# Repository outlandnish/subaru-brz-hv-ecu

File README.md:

# Subaru BRZ HV ECU

> **SAFETY NOTICE:** This system controls high-voltage contactors on a traction battery pack.
> Incorrect firmware can result in arc flash, fire, or electrocution. Do not flash untested builds
> to hardware connected to a live HV pack.

This is the HV ECU for a Subaru BRZ EV conversion. It manages:
- **Battery management** — cell voltage monitoring, balancing, and protection via NXP MC33772 BCC ICs
- **HV contactor control** — precharge, engage, and safe shutdown via DRV8874 H-bridge drivers
- **CAN communication** — IVT-S current/voltage shunt (HV CAN), CHAdeMO EVSE controller (M3 CAN)
- **CANopen** — parameter access and spot-value reporting via libopeninv

## Hardware

See [`hardware/`](hardware/) for schematics and pin maps.

Key specs:
- MCU: STM32F413VH running FreeRTOS
- 16 Taycan modules (8 per BCC chain, two MC33772 chains)
- DRV8874 H-bridge drivers for HV and AC contactors
- IVT-S 1000 A current shunt on HV CAN bus
- CHAdeMO controller (Foccci) on M3 CAN bus

## Getting Started

Clone with submodules:

```bash
git clone --recurse-submodules <repo-url>
# or after a plain clone:
git submodule update --init --recursive
```

## Building and Flashing

This project uses [PlatformIO](https://platformio.org/).

```bash
# Build main firmware
pio run -e hv-ecu

# Flash via ST-Link
pio run -e hv-ecu --target upload

# Serial monitor (115200 baud)
pio device monitor
```

## First-Boot Procedure

1. Flash firmware with ST-Link connected and HV pack **disconnected**.
2. Open a serial monitor at 115200 baud.
3. Type `status` to verify BCC devices are detected and cell voltages are sensible.
4. Type `params` to review default charge parameters before connecting HV.
5. Connect HV pack. Type `hv connect` to initiate precharge sequence.

## Running Tests

Unit tests run on-target via PlatformIO Unity:

```bash
pio test -e bms-test
```

## License

MIT — see [LICENSE](LICENSE).

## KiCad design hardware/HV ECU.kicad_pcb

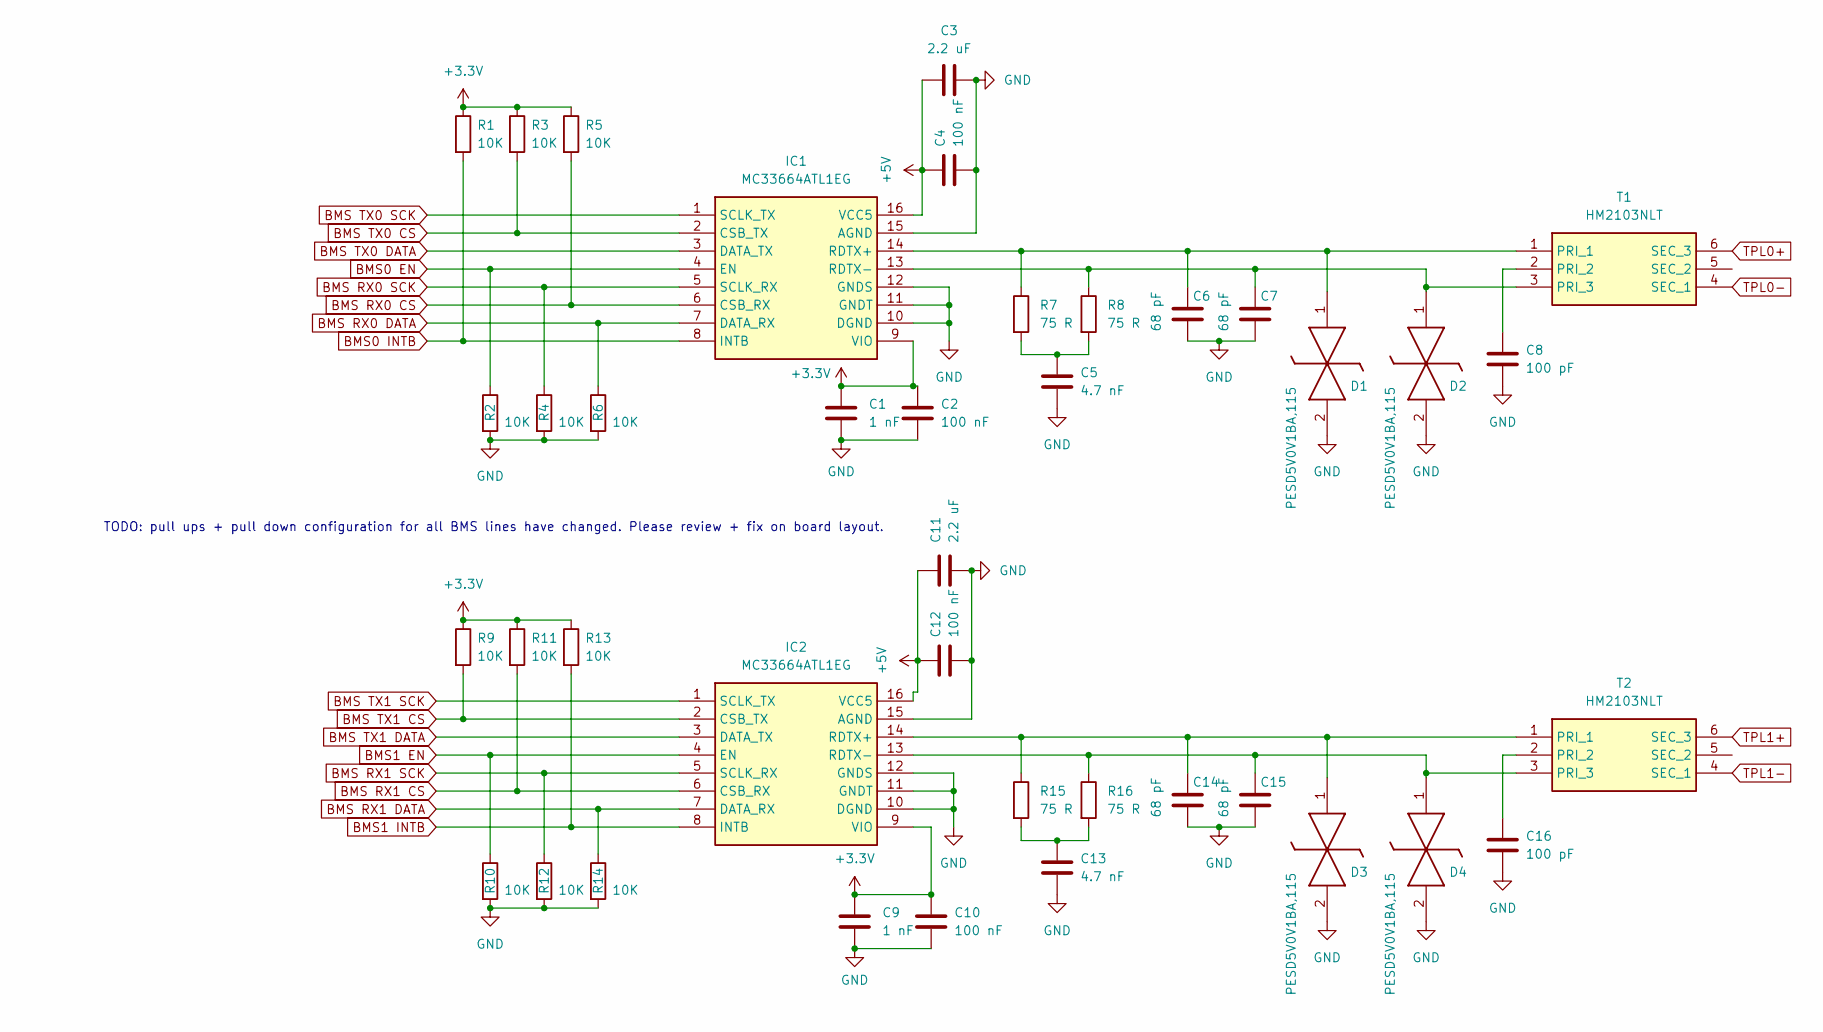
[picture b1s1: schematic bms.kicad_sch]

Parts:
C1, C9: 1 nF; C_0402_1005Metric
C2, C4, C10, C12: 100 nF; C_0402_1005Metric
C3, C11: 2.2 uF; C_0805_2012Metric
C5, C13: 4.7 nF; C_0402_1005Metric
C6, C7, C14, C15: 68 pF; C_0402_1005Metric
C8, C16: 100 pF; C_0402_1005Metric
D1, D2, D3, D4: PESD5V0V1BA,115; SOD2512X110N; Mouser Part Number 771-PESD5V0V1771-BA
IC1, IC2: MC33664ATL1EG; SOIC127P600X175-16N; Mouser Part Number 841-MC33664ATL1EG
R1, R2, R3, R4, R5, R6, R9, R10, R11, R12, R13, R14: 10K; C_0402_1005Metric
R7, R8, R15, R16: 75 R; C_0603_1608Metric
T1, T2: HM2103NLT; SOP254P940X572-6N; Mouser Part Number 673-HM2103NLT

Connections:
+3.3V: C1.1, C2.1, C9.1, C10.1, IC1.9 (VIO), IC2.9 (VIO), R1.1, R3.1, R5.1, R9.1, R11.1, R13.1; also elsewhere on the board
+5V: C3.1, C4.1, C11.1, C12.1, IC1.16 (VCC5), IC2.16 (VCC5); also elsewhere on the board
BMS0 EN: IC1.4 (EN), R2.1
BMS0 INTB: IC1.8 (INTB), R1.2
BMS1 EN: IC2.4 (EN), R10.1
BMS1 INTB: IC2.8 (INTB), R13.2
BMS RX0 CS: IC1.6 (CSB_RX), R5.2
BMS RX0 DATA: IC1.7 (DATA_RX), R6.1
BMS RX0 SCK: IC1.5 (SCLK_RX), R4.1
BMS RX1 CS: IC2.6 (CSB_RX), R11.2
BMS RX1 DATA: IC2.7 (DATA_RX), R14.1
BMS RX1 SCK: IC2.5 (SCLK_RX), R12.1
BMS TX0 CS: IC1.2 (CSB_TX), R3.2
BMS TX0 DATA: IC1.3 (DATA_TX)
BMS TX0 SCK: IC1.1 (SCLK_TX)
BMS TX1 CS: IC2.2 (CSB_TX), R9.2
BMS TX1 DATA: IC2.3 (DATA_TX)
BMS TX1 SCK: IC2.1 (SCLK_TX)
GND: C1.2, C2.2, C3.2, C4.2, C5.2, C6.2, C7.2, C8.2, C9.2, C10.2, C11.2, C12.2, C13.2, C14.2, C15.2, C16.2, D1.2 (K2), D2.2 (K2), D3.2 (K2), D4.2 (K2), IC1.10 (DGND), IC1.11 (GNDT), IC1.12 (GNDS), IC1.15 (AGND), IC2.10 (DGND), IC2.11 (GNDT), IC2.12 (GNDS), IC2.15 (AGND), R2.2, R4.2, R6.2, R10.2, R12.2, R14.2; also elsewhere on the board
unnamed: C5.1, R7.2, R8.2
unnamed: C13.1, R15.2, R16.2
unnamed: C6.1, D1.1 (K1), IC1.14 (RDTX+), R7.1, T1.1 (PRI_1)
unnamed: C7.1, D2.1 (K1), IC1.13 (RDTX-), R8.1, T1.3 (PRI_3)
unnamed: C14.1, D3.1 (K1), IC2.14 (RDTX+), R15.1, T2.1 (PRI_1)
unnamed: C15.1, D4.1 (K1), IC2.13 (RDTX-), R16.1, T2.3 (PRI_3)
unnamed: C8.1, T1.2 (PRI_2)
unnamed: C16.1, T2.2 (PRI_2)
TPL0+: T1.6 (SEC_3); also elsewhere on the board
TPL0-: T1.4 (SEC_1); also elsewhere on the board
TPL1+: T2.6 (SEC_3); also elsewhere on the board
TPL1-: T2.4 (SEC_1); also elsewhere on the board

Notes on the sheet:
TODO: pull ups + pull down configuration for all BMS lines have changed. Please review + fix on board layout.

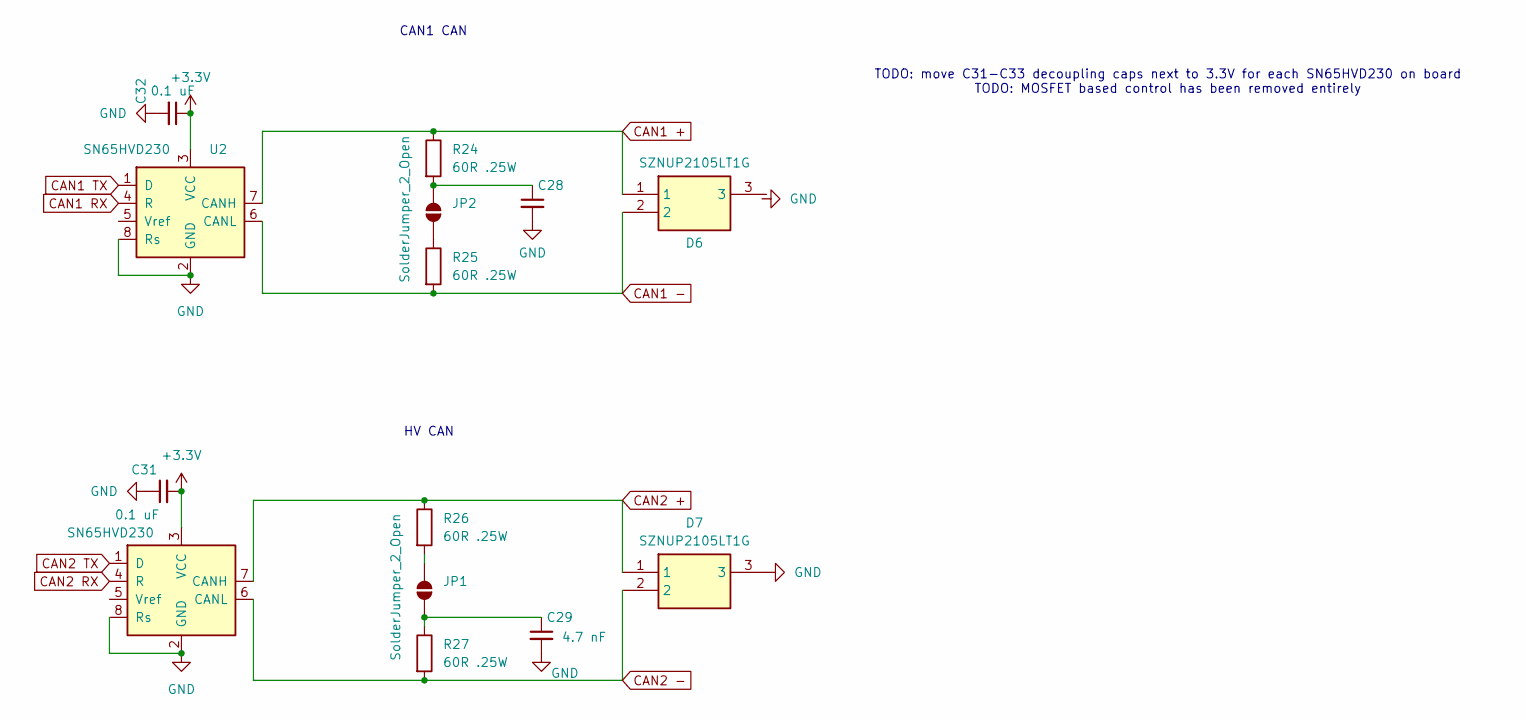
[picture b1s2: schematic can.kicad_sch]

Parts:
C28, C29: 4.7 nF; C_0402_1005Metric
C31, C32: 0.1 uF; C_0402_1005Metric
D6, D7: SZNUP2105LT1G; SOT-23_ONS; Mouser Part Number 863-SZNUP2105LT1G
JP1, JP2: SolderJumper_2_Open; SolderJumper-2_P1.3mm_Open_RoundedPad1.0x1.5mm
R24, R25, R26, R27: 60R .25W; R_0603_1608Metric
U2, U3: SN65HVD230; SOIC-8_3.9x4.9mm_P1.27mm

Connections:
+3.3V: C31.2, C32.1, U2.3 (VCC), U3.3 (VCC); also elsewhere on the board
CAN1 +: D6.1, R24.1, U2.7 (CANH); also elsewhere on the board
CAN1 -: D6.2, R25.2, U2.6 (CANL); also elsewhere on the board
CAN1 RX: U2.4 (R); also elsewhere on the board
CAN1 TX: U2.1 (D); also elsewhere on the board
CAN2 +: D7.1, R26.1, U3.7 (CANH); also elsewhere on the board
CAN2 -: D7.2, R27.2, U3.6 (CANL); also elsewhere on the board
CAN2 RX: U3.4 (R); also elsewhere on the board
CAN2 TX: U3.1 (D); also elsewhere on the board
GND: C28.2, C29.2, C31.1, C32.2, D7.3, U2.2 (GND), U2.8 (Rs), U3.2 (GND), U3.8 (Rs); also elsewhere on the board
unnamed: C29.1, JP1.1 (A), R27.1
unnamed: JP1.2 (B), R26.2
unnamed: JP2.1 (A), R25.1
unnamed: C28.1, JP2.2 (B), R24.2

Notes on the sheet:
CAN1 CAN
HV CAN
TODO: move C31-C33 decoupling caps next to 3.3V for each SN65HVD230 on board TODO: MOSFET based control has been removed entirely

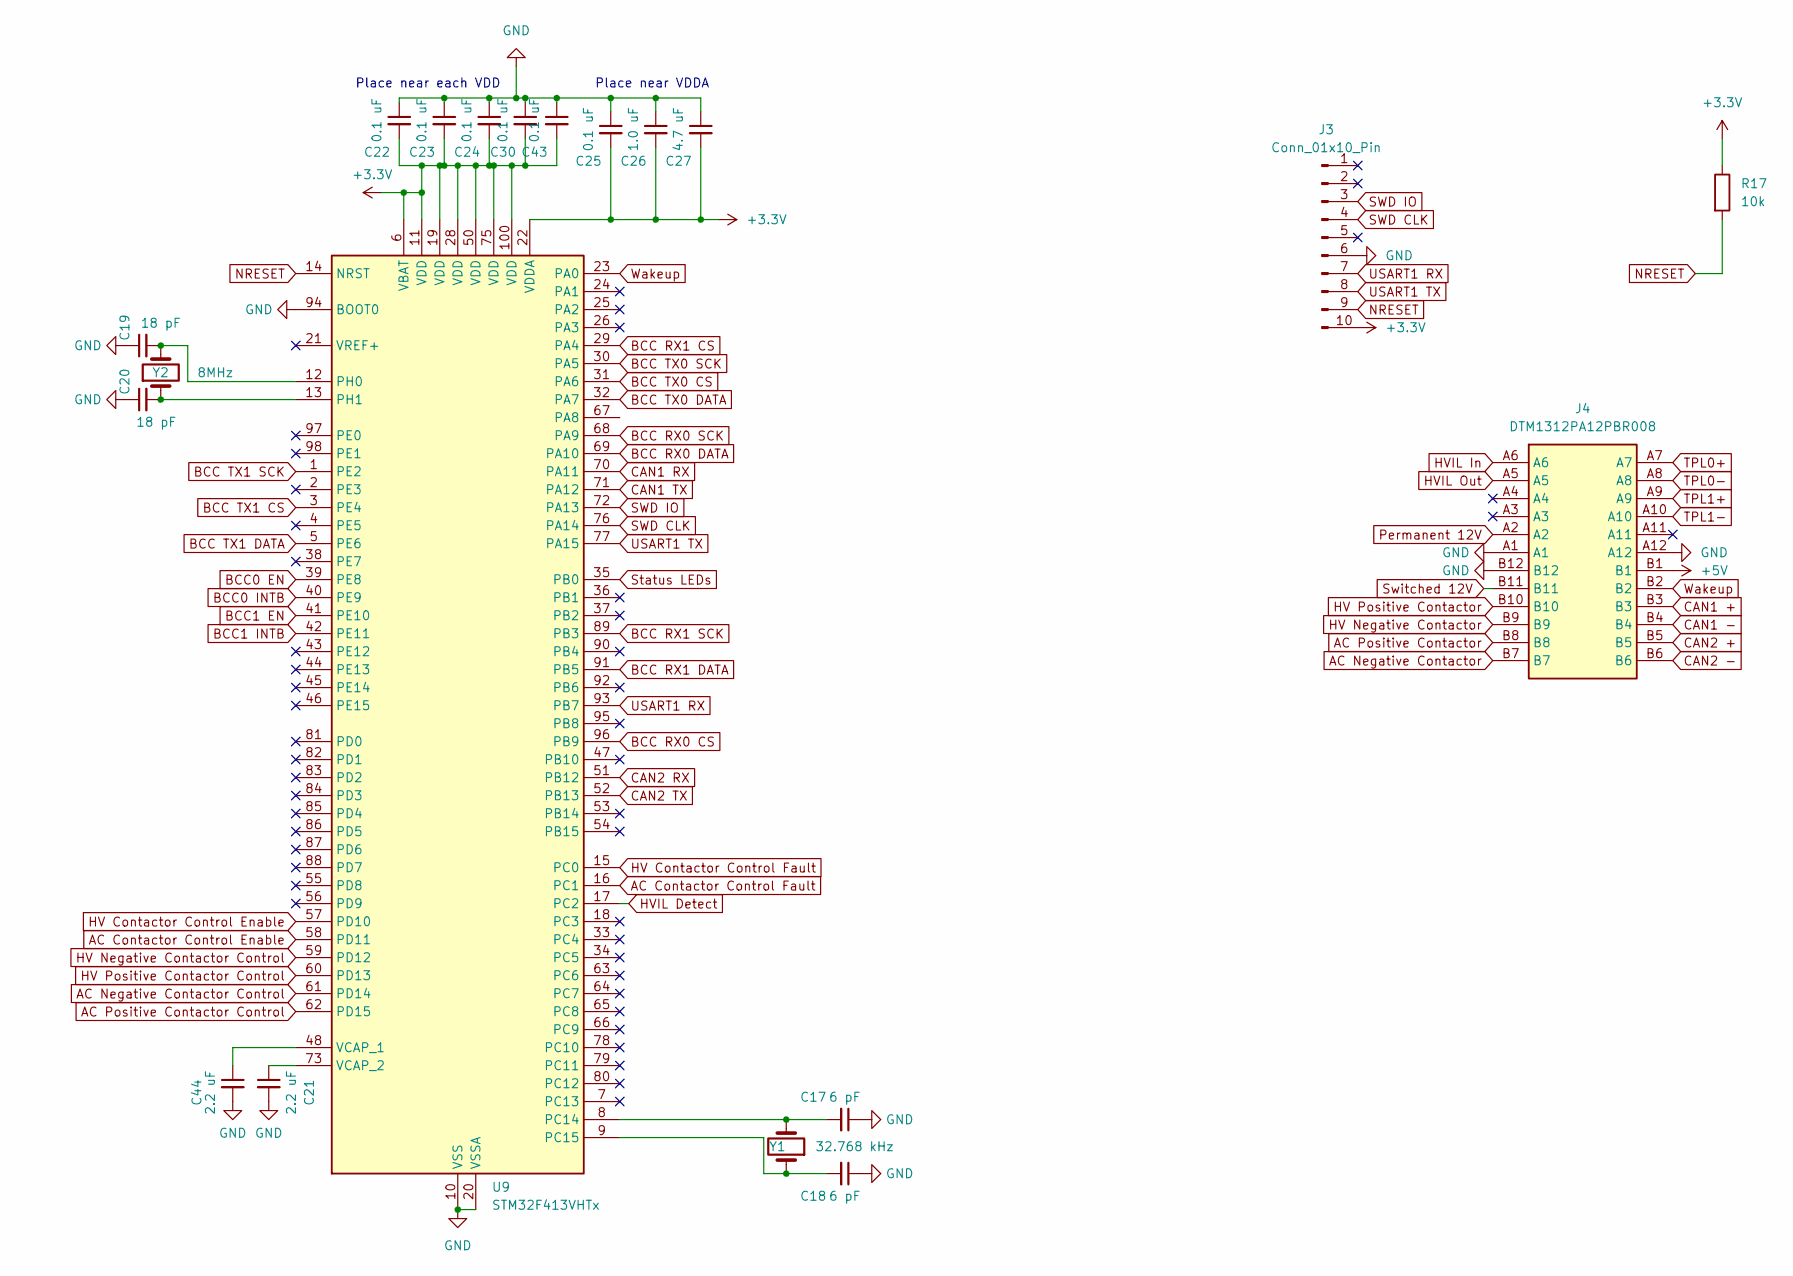
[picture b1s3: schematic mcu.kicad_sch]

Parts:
C17, C18: 6 pF; C_0402_1005Metric
C19, C20: 18 pF; C_0402_1005Metric
C21, C44: 2.2 uF; C_0805_2012Metric
C22, C23, C24, C25, C30, C43: 0.1 uF; C_0402_1005Metric
C26: 1.0 uF; C_0402_1005Metric
C27: 4.7 uF; C_0805_2012Metric
J3: Conn_01x10_Pin; ST-Link MINIV3 BTB
J4: DTM1312PA12PBR008; Mouser Part Number 571-TM1312PA12PBR008
R17: 10k; R_0603_1608Metric
U9: STM32F413VHTx; LQFP-100_14x14mm_P0.5mm
Y1: 32.768 kHz; Crystal_SMD_3215-2Pin_3.2x1.5mm
Y2: 8MHz; Crystal_SMD_HC49-SD

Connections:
+3.3V: C22.2, C23.2, C24.2, C25.2, C26.2, C27.2, C30.2, C43.2, J3.10, R17.1, U9.6 (VBAT), U9.11 (VDD), U9.19 (VDD), U9.22 (VDDA), U9.28 (VDD), U9.50 (VDD), U9.75 (VDD), U9.100 (VDD); also elsewhere on the board
+5V: J4.B1; also elsewhere on the board
AC Contactor Control Enable: U9.58 (PD11); also elsewhere on the board
AC Contactor Control Fault: U9.16 (PC1); also elsewhere on the board
AC Negative Contactor: J4.B7; also elsewhere on the board
AC Negative Contactor Control: U9.61 (PD14); also elsewhere on the board
AC Positive Contactor: J4.B8; also elsewhere on the board
AC Positive Contactor Control: U9.62 (PD15); also elsewhere on the board
BCC0 EN: U9.39 (PE8)
BCC0 INTB: U9.40 (PE9)
BCC1 EN: U9.41 (PE10)
BCC1 INTB: U9.42 (PE11)
BCC RX0 CS: U9.96 (PB9)
BCC RX0 DATA: U9.69 (PA10)
BCC RX0 SCK: U9.68 (PA9)
BCC RX1 CS: U9.29 (PA4)
BCC RX1 DATA: U9.91 (PB5)
BCC RX1 SCK: U9.89 (PB3)
BCC TX0 CS: U9.31 (PA6)
BCC TX0 DATA: U9.32 (PA7)
BCC TX0 SCK: U9.30 (PA5)
BCC TX1 CS: U9.3 (PE4)
BCC TX1 DATA: U9.5 (PE6)
BCC TX1 SCK: U9.1 (PE2)
CAN1 +: J4.B3; also elsewhere on the board
CAN1 -: J4.B4; also elsewhere on the board
CAN1 RX: U9.70 (PA11); also elsewhere on the board
CAN1 TX: U9.71 (PA12); also elsewhere on the board
CAN2 +: J4.B5; also elsewhere on the board
CAN2 -: J4.B6; also elsewhere on the board
CAN2 RX: U9.51 (PB12); also elsewhere on the board
CAN2 TX: U9.52 (PB13); also elsewhere on the board
GND: C17.1, C18.1, C19.1, C20.1, C21.2, C22.1, C23.1, C24.1, C25.1, C26.1, C27.1, C30.1, C43.1, C44.2, J3.6, J4.A1, J4.A12, J4.B12, U9.10 (VSS), U9.20 (VSSA), U9.27 (VSS), U9.49 (VSS), U9.74 (VSS), U9.94 (BOOT0), U9.99 (VSS); also elsewhere on the board
HV Contactor Control Enable: U9.57 (PD10); also elsewhere on the board
HV Contactor Control Fault: U9.15 (PC0); also elsewhere on the board
HV Negative Contactor: J4.B9; also elsewhere on the board
HV Negative Contactor Control: U9.59 (PD12); also elsewhere on the board
HV Positive Contactor: J4.B10; also elsewhere on the board
HV Positive Contactor Control: U9.60 (PD13); also elsewhere on the board
HVIL Detect: U9.17 (PC2); also elsewhere on the board
HVIL In: J4.A6; also elsewhere on the board
NRESET: J3.9, R17.2, U9.14 (NRST)
unnamed: C17.2, U9.8 (PC14), Y1.2
unnamed: C18.2, U9.9 (PC15), Y1.1
unnamed: C19.2, U9.12 (PH0), Y2.2
unnamed: C20.2, U9.13 (PH1), Y2.1
unnamed: C44.1, U9.48 (VCAP_1)
unnamed: C21.1, U9.73 (VCAP_2)
Permanent 12V: J4.A2; also elsewhere on the board
SWD CLK: J3.4, U9.76 (PA14)
SWD IO: J3.3, U9.72 (PA13)
Status LEDs: U9.35 (PB0); also elsewhere on the board
Switched 12V: J4.B11; also elsewhere on the board
TPL0+: J4.A7; also elsewhere on the board
TPL0-: J4.A8; also elsewhere on the board
TPL1+: J4.A9; also elsewhere on the board
TPL1-: J4.A10; also elsewhere on the board
USART1 RX: J3.7, U9.93 (PB7)
USART1 TX: J3.8, U9.77 (PA15)
Wakeup: J4.B2, U9.23 (PA0)

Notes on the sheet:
Place near each VDD
Place near VDDA

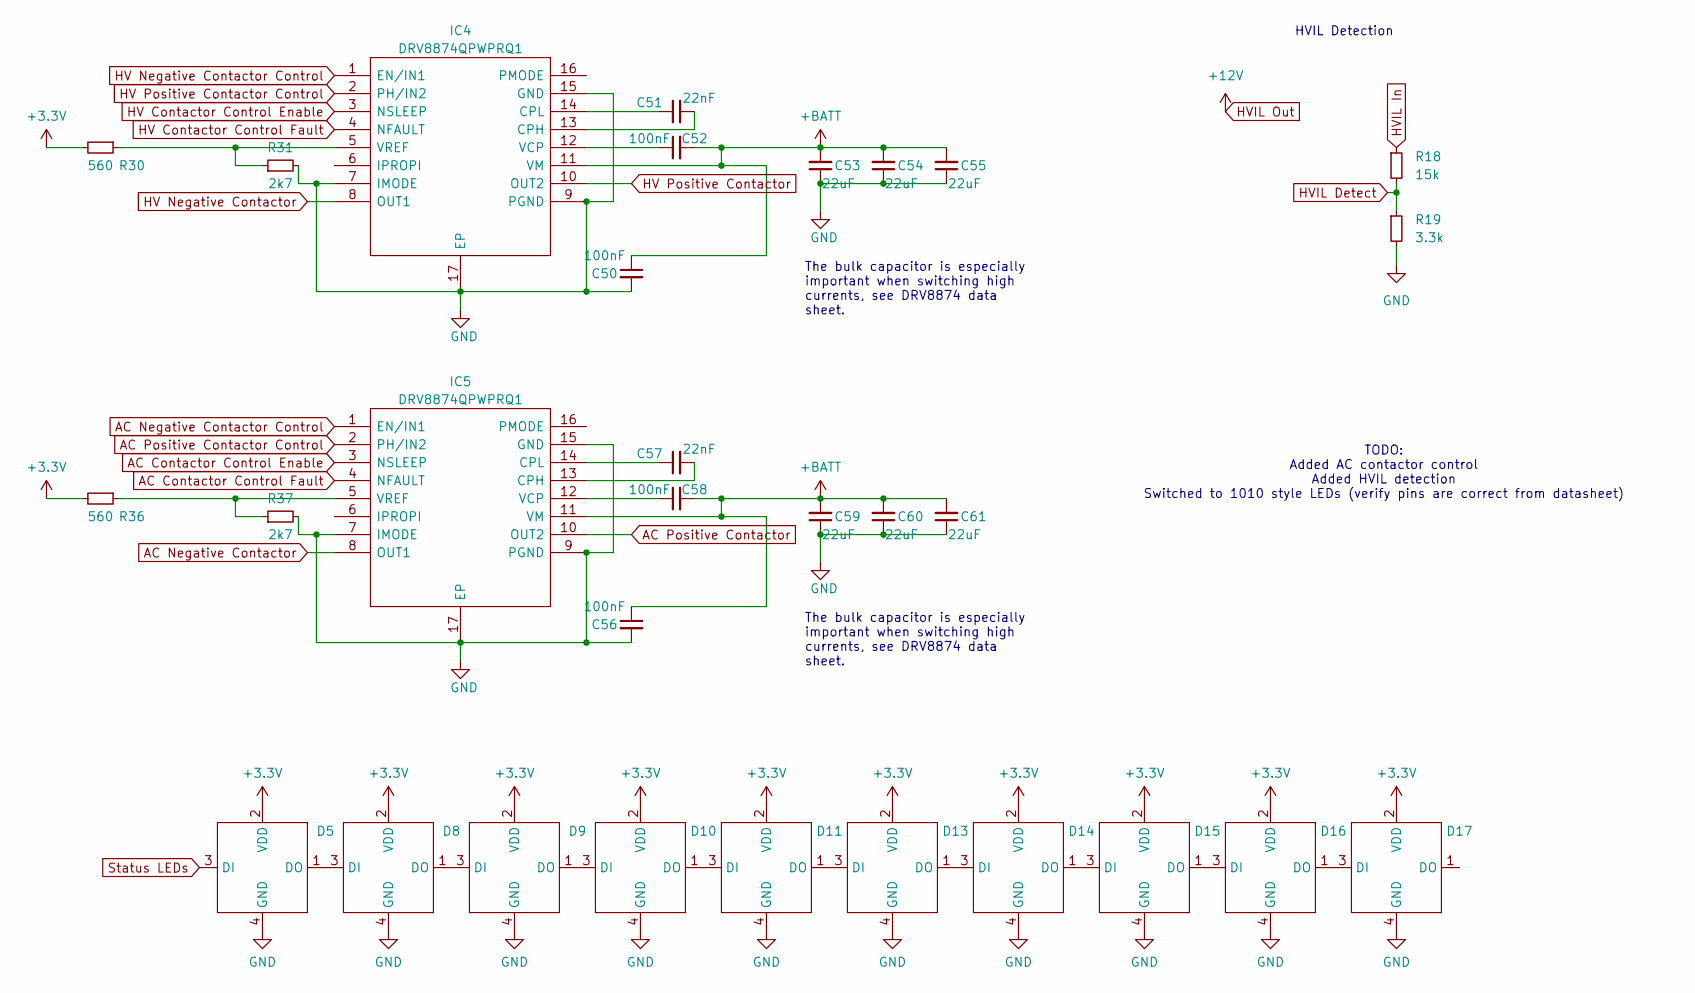
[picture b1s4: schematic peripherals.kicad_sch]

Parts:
C50, C52, C56, C58: 100nF; C_0805_2012Metric_Pad1.18x1.45mm_HandSolder; LCSC C49678
C51, C57: 22nF; C_0805_2012Metric_Pad1.18x1.45mm_HandSolder; LCSC C1729
C53, C54, C55, C59, C60, C61: 22uF; C_1210_3225Metric_Pad1.33x2.70mm_HandSolder; LCSC C12891
D5, D8, D9, D10, D11, D13, D14, D15, D16, D17: XL-1010RGBC-WS2812B
IC4, IC5: DRV8874QPWPRQ1; SOP65P640X120-17N; Mouser Part Number 595-DRV8874QPWPRQ1
R18: 15k; R_0402_1005Metric_Pad0.72x0.64mm_HandSolder
R19: 3.3k; R_0402_1005Metric_Pad0.72x0.64mm_HandSolder
R30, R36: 560; R_0805_2012Metric_Pad1.20x1.40mm_HandSolder; LCSC C28636
R31, R37: 2k7; R_0805_2012Metric_Pad1.20x1.40mm_HandSolder; LCSC C17530

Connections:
+3.3V: D5.2 (VDD), D8.2 (VDD), D9.2 (VDD), D10.2 (VDD), D11.2 (VDD), D13.2 (VDD), D14.2 (VDD), D15.2 (VDD), D16.2 (VDD), D17.2 (VDD), R30.2, R36.2; also elsewhere on the board
+BATT: C50.1, C52.2, C53.2, C54.2, C55.2, C56.1, C58.2, C59.2, C60.2, C61.2, IC4.11 (VM), IC5.11 (VM); also elsewhere on the board
AC Contactor Control Enable: IC5.3 (NSLEEP); also elsewhere on the board
AC Contactor Control Fault: IC5.4 (NFAULT); also elsewhere on the board
AC Negative Contactor: IC5.8 (OUT1); also elsewhere on the board
AC Negative Contactor Control: IC5.1 (EN/IN1); also elsewhere on the board
AC Positive Contactor: IC5.10 (OUT2); also elsewhere on the board
AC Positive Contactor Control: IC5.2 (PH/IN2); also elsewhere on the board
GND: C50.2, C53.1, C54.1, C55.1, C56.2, C59.1, C60.1, C61.1, D5.4 (GND), D8.4 (GND), D9.4 (GND), D10.4 (GND), D11.4 (GND), D13.4 (GND), D14.4 (GND), D15.4 (GND), D16.4 (GND), D17.4 (GND), IC4.7 (IMODE), IC4.9 (PGND), IC4.15 (GND), IC4.17 (EP), IC5.7 (IMODE), IC5.9 (PGND), IC5.15 (GND), IC5.17 (EP), R19.2, R31.2, R37.2; also elsewhere on the board
HV Contactor Control Enable: IC4.3 (NSLEEP); also elsewhere on the board
HV Contactor Control Fault: IC4.4 (NFAULT); also elsewhere on the board
HV Negative Contactor: IC4.8 (OUT1); also elsewhere on the board
HV Negative Contactor Control: IC4.1 (EN/IN1); also elsewhere on the board
HV Positive Contactor: IC4.10 (OUT2); also elsewhere on the board
HV Positive Contactor Control: IC4.2 (PH/IN2); also elsewhere on the board
HVIL Detect: R18.2, R19.1; also elsewhere on the board
HVIL In: R18.1; also elsewhere on the board
unnamed: D5.1 (DO), D8.3 (DI)
unnamed: D8.1 (DO), D9.3 (DI)
unnamed: D9.1 (DO), D10.3 (DI)
unnamed: D10.1 (DO), D11.3 (DI)
unnamed: D11.1 (DO), D13.3 (DI)
unnamed: D13.1 (DO), D14.3 (DI)
unnamed: D14.1 (DO), D15.3 (DI)
unnamed: D15.1 (DO), D16.3 (DI)
unnamed: D16.1 (DO), D17.3 (DI)
unnamed: C51.2, IC4.13 (CPH)
unnamed: C51.1, IC4.14 (CPL)
unnamed: C52.1, IC4.12 (VCP)
unnamed: IC4.5 (VREF), R30.1, R31.1
unnamed: C57.2, IC5.13 (CPH)
unnamed: C57.1, IC5.14 (CPL)
unnamed: C58.1, IC5.12 (VCP)
unnamed: IC5.5 (VREF), R36.1, R37.1
Status LEDs: D5.3 (DI); also elsewhere on the board

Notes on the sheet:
HVIL Detection
The bulk capacitor is especially important when switching high currents, see DRV8874 data sheet.
TODO: Added AC contactor control Added HVIL detection Switched to 1010 style LEDs (verify pins are correct from datasheet)

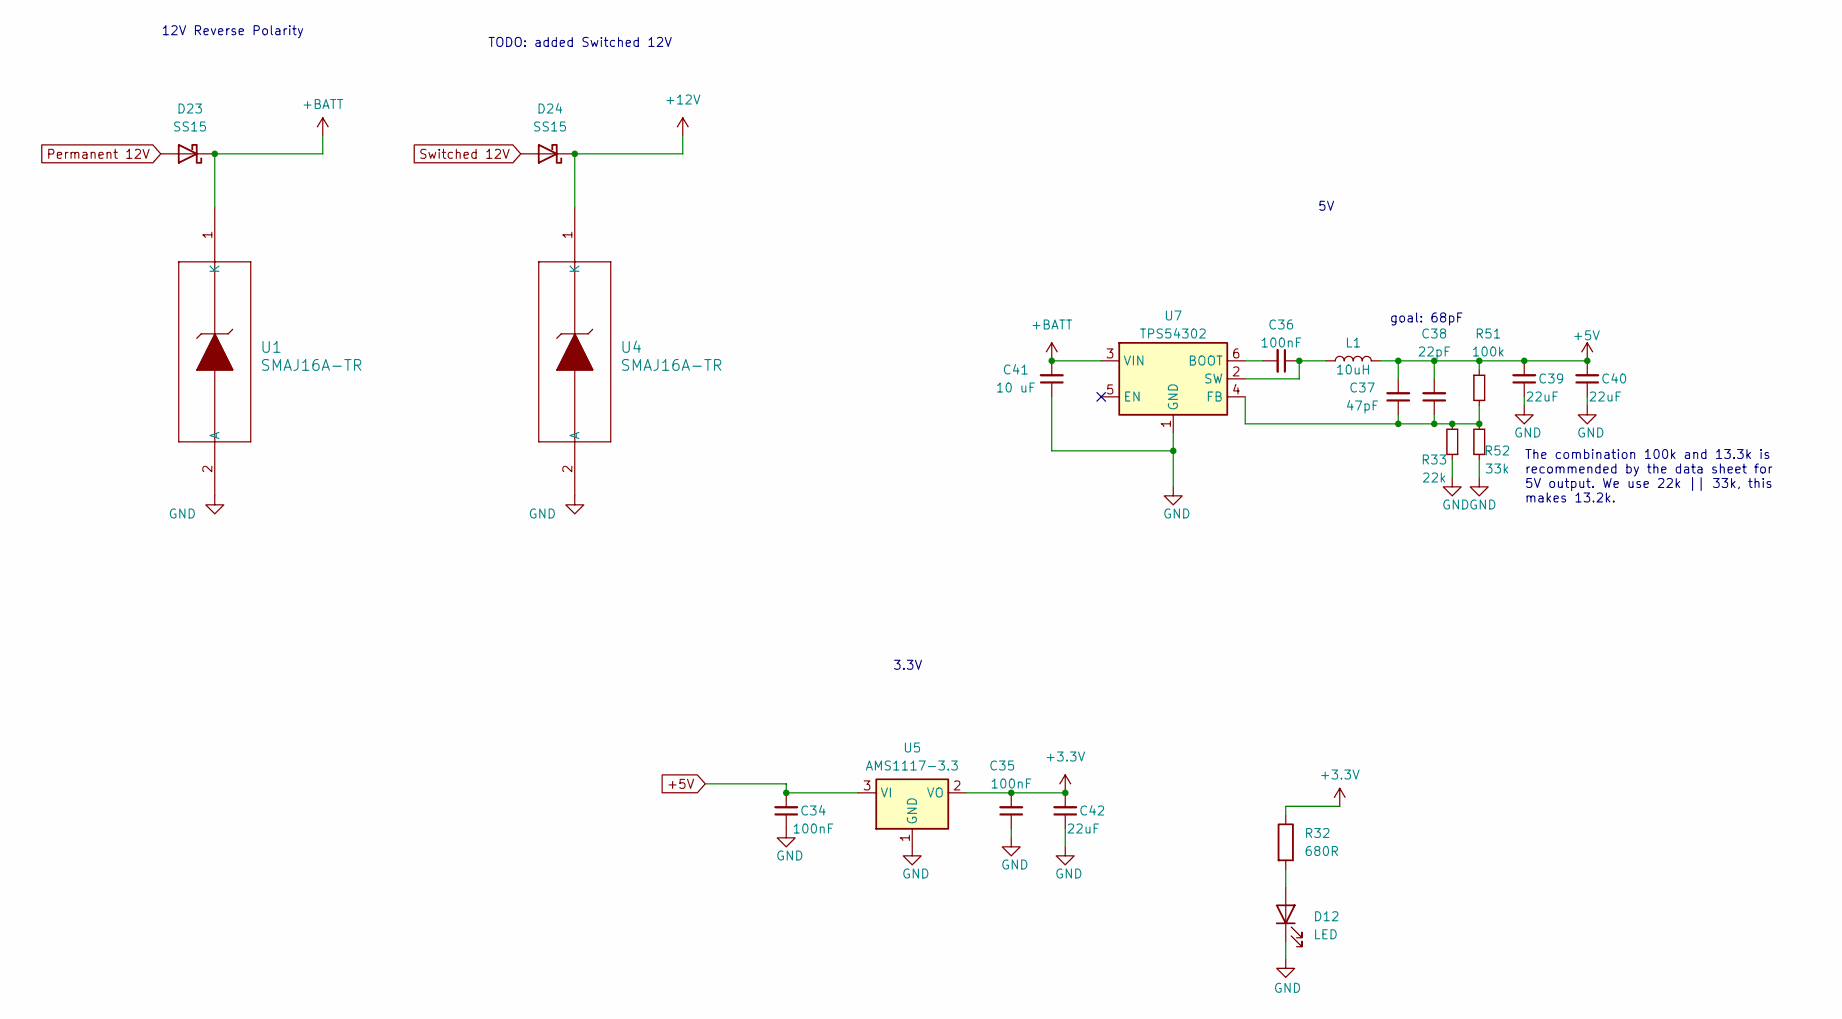
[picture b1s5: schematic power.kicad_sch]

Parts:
C34, C35, C36: 100nF; C_0805_2012Metric_Pad1.18x1.45mm_HandSolder; LCSC C49678
C37: 47pF; C_0805_2012Metric_Pad1.18x1.45mm_HandSolder; LCSC C14857
C38: 22pF; C_0805_2012Metric_Pad1.18x1.45mm_HandSolder; LCSC C1804
C39, C40, C42: 22uF; C_1210_3225Metric_Pad1.33x2.70mm_HandSolder; LCSC C12891
C41: 10 uF; C_0805_2012Metric_Pad1.18x1.45mm_HandSolder; LCSC C14857
D12: LED; D_0603_1608Metric
D23, D24: SS15; D_SMA
L1: 10uH; L_6.3x6.3_H3; LCSC C408412
R32: 680R; R_0603_1608Metric
R33: 22k; R_0805_2012Metric_Pad1.20x1.40mm_HandSolder; LCSC C17560
R51: 100k; R_0805_2012Metric_Pad1.20x1.40mm_HandSolder; LCSC C149504
R52: 33k; R_0805_2012Metric_Pad1.20x1.40mm_HandSolder; LCSC C17633
U1, U4: SMAJ16A-TR; SMA_UNI_STM; LCSC C908770
U5: AMS1117-3.3; SOT-223-3_TabPin2; LCSC C6186
U7: TPS54302; SOT-23-6; LCSC C311983

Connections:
+3.3V: C35.2, C42.2, R32.1, U5.2 (VO); also elsewhere on the board
+5V: C34.2, C37.2, C38.2, C39.2, C40.2, L1.2, R51.1, U5.3 (VI); also elsewhere on the board
+BATT: C41.2, D23.1 (K), U1.1 (K), U7.3 (VIN); also elsewhere on the board
GND: C34.1, C35.1, C39.1, C40.1, C41.1, C42.1, D12.1 (K), R33.1, R52.1, U1.2 (A), U4.2 (A), U5.1 (GND), U7.1 (GND); also elsewhere on the board
unnamed: D12.2 (A), R32.2
unnamed: C36.2, U7.6 (BOOT)
unnamed: C37.1, C38.1, R33.2, R51.2, R52.2, U7.4 (FB)
unnamed: C36.1, L1.1, U7.2 (SW)
Permanent 12V: D23.2 (A); also elsewhere on the board
Switched 12V: D24.2 (A); also elsewhere on the board

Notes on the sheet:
goal: 68pF
12V Reverse Polarity
3.3V
TODO: added Switched 12V
The combination 100k and 13.3k is recommended by the data sheet for 5V output. We use 22k || 33k, this makes 13.2k.

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
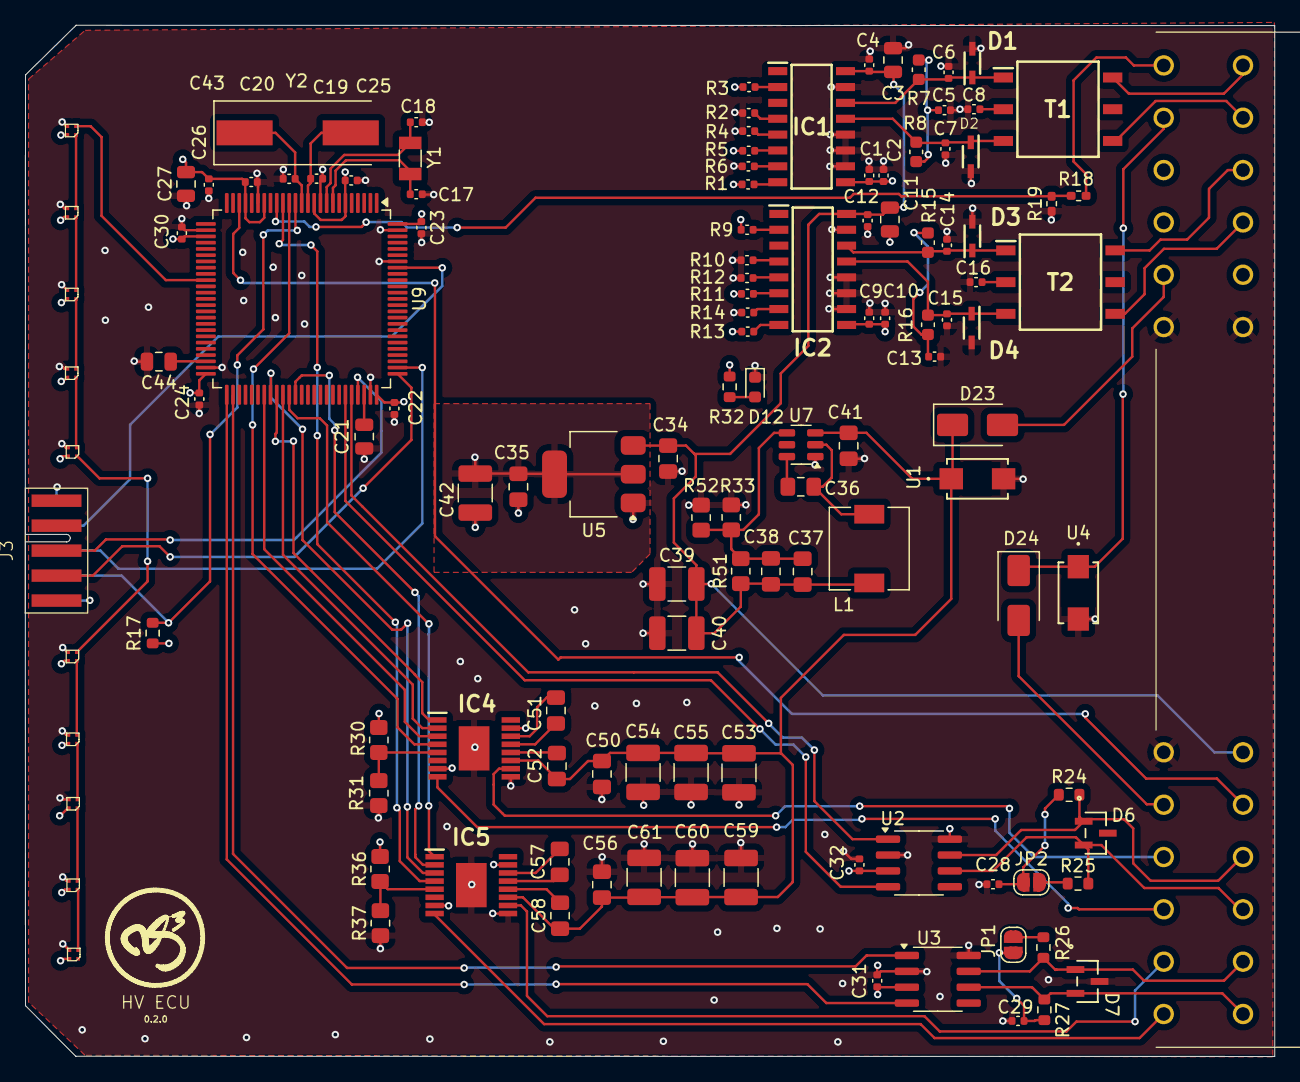
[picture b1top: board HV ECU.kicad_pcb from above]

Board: 4 copper layers, 100.0 x 82.6 mm, 125 parts (0 on the bottom side), 91 nets.

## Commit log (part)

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2025-10-25 initial commit - working state for monitoring single bcc chain
2025-10-26 basic BMS implementation (single pack with charge control)
2025-10-26 added function to dump the registers
2025-10-31 wip: uds / bootloader exploration
2025-11-03 basic evse status implementation. added ISA shunt implementation
2025-11-03 organize code a bit
2025-11-04 more re-organization. Added top level bcc command
2025-11-04 Updated submodules and battery_char env
2025-11-05 Updated PCS implementation
2025-11-05 Re-enable main
2025-11-12 Simple charger interface
2025-11-12 updated bcc lib
2025-11-16 Updated can clock speed for prescaler
2025-11-16 Moved pcs into it's own library and remove UDS implementation for now
2025-11-16 Removed EVSE implementation
2025-11-16 Implement libopeninv as an Arduino compatible library
2025-11-16 chademo implementation
2025-11-16 Remove bootloader project for now
2025-11-16 Update BMS + main to use Chademo implementation
2025-11-17 Fixed CanOpen communication
2025-11-17 Remove IPC can references
2025-11-17 can sdo fixes
2025-11-17 IVT defaults testing
2025-11-17 Updated openinverter implementation
2025-11-17 quality of life improvements
2025-11-17 Update script
2025-11-17 Undo change for crc
2025-11-17 Save confirmations + updated readme
2025-11-17 Fixed saves
2025-12-02 Add 0.2.0 hardware
2025-12-02 Update bcc library
